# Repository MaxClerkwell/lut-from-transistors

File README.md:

# A look-up table built from transistors

A LUT with two inputs, the logic element of an FPGA, built from 20 MOS
transistors. The circuit is described in Python with
[SKiDL](https://devbisme.github.io/skidl/), drawn as a KiCad schematic,
simulated with ngspice, and the result is written as a VCD file that opens
in [GTKWave](https://gtkwave.sourceforge.net/).

```
SKiDL (lut.py)  ->  KiCad schematic  ->  ngspice  ->  VCD  ->  GTKWave
```

To run it yourself, see [Running the simulation](#running-the-simulation).

## What a LUT is

A LUT with k inputs does not compute anything. It stores the truth table of
a logic function in 2^k memory bits, and its inputs select which of these
bits appears at the output. With two inputs there are four bits and
therefore 16 possible functions, from AND to XOR, all realised by the same
hardware. Only the stored bits differ. That is what makes an FPGA
programmable.

```
T0 --[A=0]--+
            +-- N0 --[B=0]--+
T1 --[A=1]--+               +-- YI --|>o--|>o-- Y
T2 --[A=0]--+               |
            +-- N1 --[B=1]--+
T3 --[A=1]--+
```

The selection is a tree of 2:1 multiplexers, one level per input. The table
index is `2 B + A`. A buffer of two inverters restores the level and drives
the load.

## Configuration by voltage sources

The four table bits T0 to T3 are the configuration of the LUT. Here they
are voltage sources: 0 V for a 0, 5 V for a 1. In an FPGA they are memory
cells written by the bitstream. Replacing the cells by sources keeps the
circuit small and makes the configuration visible in the schematic: the
function of the LUT is the pattern of the four source values. The
simulation rewrites these sources every 800 ns and so steps through all 16
functions in one run.

## The switches

Each switch of the multiplexers is a transmission gate: an NMOS and a PMOS
in parallel, driven by complementary select signals. An NMOS alone passes
a 0 well but hands over a 1 only up to its gate voltage minus its
threshold; a PMOS alone has the opposite problem. Together they pass both
levels without loss, and the internal node YI reaches the full supply.
The price is one extra transistor per switch and the complements AN and BN
of the inputs, made by two inverters.

| Part | Transistors |
|---|---|
| 6 switches, 2 transistors each | 12 |
| 2 inverters for AN and BN | 4 |
| output buffer, 2 inverters | 4 |
| total | 20 |

## A hierarchical schematic

The schematic is hierarchical. Every building block is drawn once, on a
sheet of its own, and used as often as needed.

| Sheet | File | Content | Used |
|---|---|---|---|
| `lut2` | `lut2.kicad_sch` | sources, load, and the sheets below | 1 |
| `inverter` | `inverter.kicad_sch` | one PMOS, one NMOS | 4 |
| `mux2` | `mux2.kicad_sch` | two switches | 3 |
| `switch` | `switch.kicad_sch` | one transmission gate | 6 |
| `buffer` | `buffer.kicad_sch` | two inverters | 1 |

Five files describe 15 sheets. The hierarchy is three levels deep: the
transistors of a switch sit in `lut2 / mux_n0 / sw0`.

The root sheet shows the structure of the LUT: the supply, the inputs, the
four configuration sources, two inverters for the complements of the
inputs, two multiplexers selected by A, one selected by B, and the buffer.

In KiCad a sheet that is used several times stores the references of its
symbols once per use. The transistors of `switch.kicad_sch` are Q5 and Q6
in `mux_n0 / sw0` and Q15 and Q16 in `mux_y / sw1`. `hier.py` takes care
of this: it walks the hierarchy, creates the flat SKiDL circuit and writes
every sheet with the references of all its uses.

## Results

The LUT computes all 16 functions correctly: 64 of 64 table entries. All
numbers below are written by `simulate.py` to `results/summary.md`.

| Quantity | Value |
|---|---|
| Level of the internal node YI for a 1 | 5.00 V |
| Level of the output Y for a 1 | 5.00 V |
| Supply current at rest, largest | 0.015 µA |
| Delay A to Y, rising / falling | 12.2 ns / 9.1 ns |
| Delay B to Y, rising / falling | 10.8 ns / 7.8 ns |
| Delay table bit to Y, rising / falling | 11.1 ns / 8.2 ns |

What the numbers show:

- **The transmission gates pass the full level.** The internal node YI
  reaches 5 V for a 1 and 0 V for a 0, so the first inverter of the buffer
  is fully switched and the circuit draws almost no current at rest.
- **The input of the last level is the fastest.** A signal at B passes one
  multiplexer, a signal at A passes two. B is faster by about 1.4 ns.
  Synthesis tools use this and route timing-critical signals to the fast
  inputs of a LUT.
- **A change of configuration is as fast as a change of input.** A table
  bit passes two multiplexers, like A, and arrives at Y after a similar
  delay.

The plot shows one function window of 800 ns. During the first 100 ns the
table still holds the previous function; it is rewritten at 100 ns.

### Glitches

If both inputs change at the same instant, the multiplexer tree passes
through an intermediate state, even if the old and the new table entry are
the same. `simulate.py` tests this in a second run.

| Change | Lowest level of YI | Lowest level of Y |
|---|---|---|
| XOR, index 1 to 2 | 3.37 V | 5.00 V |
| XOR, index 2 to 1 | 3.58 V | 5.00 V |
| XNOR, index 0 to 3 | 3.14 V | 5.00 V |
| XNOR, index 3 to 0 | 3.74 V | 5.00 V |

The internal node dips, but the dip is too short for the buffer to follow.
With these transistors and this load no glitch reaches the output. That is
a property of this circuit, not of LUTs in general.

## Viewing the waveforms in GTKWave

```sh
gtkwave results/lut2.vcd results/lut2.gtkw
gtkwave results/lut2_glitch.vcd results/lut2_glitch.gtkw
```

The view shows the window from 4.8 µs to 5.6 µs: the table changes from
5 (NOT A) to 6 (XOR) at the marker, then the index steps through 0, 1, 3,
2, and `y` follows the table entry. The analog traces below show the
multiplexer nodes N0 and N1, the tree output YI, and the two stages of
the buffer.

The `.gtkw` file sets up the view: the table as a hexadecimal number, the
inputs, the selected index and the output as logic signals, and below them
the node voltages as analog traces.

| Signal | Kind | Content |
|---|---|---|
| `table[3:0]` | bit vector | the stored function, T3 T2 T1 T0 |
| `a`, `b`, `y` | bit | logic value, threshold at half the supply |
| `index[1:0]` | bit vector | `2 B + A`, the selected table entry |
| `v_a`, `v_b` | real | input voltages |
| `v_n0`, `v_n1` | real | outputs of the first multiplexer level |
| `v_yi` | real | output of the tree, before the buffer |
| `v_yb`, `v_y` | real | after the first and the second inverter |

VCD is a format for digital signals, but it also knows real numbers, and
GTKWave draws them as curves (Data Format, Analog). `vcd.py` is a writer of
about 100 lines without dependencies.

## The simulation

One transient run of 12.8 µs covers all 16 functions.

- The inputs step through the four combinations in Gray code, index
  0, 1, 3, 2, in steps of 200 ns. Only one input changes at a time, so
  every edge of the output can be attributed to one input.
- Every 800 ns the table bits are rewritten, 100 ns after the inputs have
  returned to 00. This is the simulation's version of loading a new
  bitstream.
- The output is sampled 5 ns before the end of every step and compared with
  the table.

The netlist that is simulated is exported from the KiCad schematic with
`kicad-cli`, which flattens the hierarchy, so the schematic is what gets
simulated.

## The paper

`paper/transistor_lut_en.tex` is a step-by-step introduction built on
this circuit: from Boolean functions and Shannon's expansion over the
transistor as a switch, the transmission gate and the CMOS inverter to
the complete LUT and its simulation, with every number in the text
computed from the model or taken from `results/summary.md`.

A GitHub Actions workflow runs on every push: it generates the schematic
in a KiCad container, checks it against the SKiDL netlist, simulates with
ngspice, checks that all 64 truth-table entries are correct, regenerates
the figures from the fresh results, builds the PDF and attaches it to
releases on version tags.

```sh
uv run scripts/make_figures.py       # figures from the model and results/
scripts/make_schematics.sh           # schematic sheets from docs/sheets/
cd paper && latexmk -pdf transistor_lut_en.tex
```

The figures are committed, so a LaTeX installation is enough to build
the PDF; the two scripts are needed only after a change of the circuit
or the simulation.

## Files

| File | Content |
|---|---|
| `lut.py` | the design: sheets `inverter`, `switch`, `mux2`, `buffer` and the root `lut2` |
| `hier.py` | hierarchy: elaborates the sheets into a flat SKiDL circuit and writes the KiCad sheets |
| `generate.py` | writes netlist and schematic, verifies the schematic against the SKiDL circuit |
| `simulate.py` | simulation, analysis, VCD and GTKWave files, plot |
| `vcd.py` | VCD writer |
| `kicad_sch.py`, `ngspice.py` | schematic writer and ngspice wrapper, from [naive-diff-amp-comperator](https://github.com/MaxClerkwell/naive-diff-amp-comperator) |
| `schematic/` | generated KiCad project: root sheet `lut2.kicad_sch`, four sub-sheets, netlist `lut2.net` |
| `docs/` | renderings: one SVG per sheet in `sheets/`, all sheets in `lut2.pdf` |
| `results/` | VCD and GTKWave files, plot, netlist, `summary.md` |
| `paper/` | the paper, `transistor_lut_en.tex`, and its figures |
| `scripts/` | `make_figures.py` and `make_schematics.sh`, the figure generators of the paper |

## Running the simulation

Requirements: [uv](https://docs.astral.sh/uv/), Python 3.10 or newer,
KiCad 9 or 10 with `kicad-cli` and the symbol libraries in
`/usr/share/kicad/symbols`, `libngspice.so.0`, and GTKWave for viewing.
`uv` installs the Python packages (SKiDL, NumPy, Matplotlib) on the first
run.

1. **Generate the schematic.** SKiDL builds the circuit from `lut.py`,
   `hier.py` writes the five KiCad sheets into `schematic/`, and
   `kicad-cli` renders them into `docs/`.

   ```sh
   uv run generate.py
   ```

   The last line must read `schematic <-> SKiDL netlist: IDENTICAL`. It
   means the schematic that KiCad reads describes the same circuit as the
   Python code. The step overwrites the schematic, including manual
   changes made in KiCad. KiCad's electrical rules check reports no
   violations.

2. **Simulate.** `kicad-cli` exports a flat SPICE netlist from the
   schematic, ngspice runs the transient analysis, and the script
   evaluates it.

   ```sh
   uv run simulate.py
   ```

   It takes a few seconds. The console ends with the truth table of all
   16 functions and the measured delays; the same text goes to
   `results/summary.md`. Along with it the script writes `results/lut2.vcd`
   and `results/lut2.gtkw`, the glitch run as `results/lut2_glitch.*`, the
   simulated netlist `results/lut2.cir` and the plot `results/lut2.png`.

3. **Open the result in GTKWave.** Give GTKWave the VCD file and the save
   file; the save file sets up the signal list and the analog traces.

   ```sh
   gtkwave results/lut2.vcd results/lut2.gtkw
   ```

   The view opens on the whole run of 12.8 µs. Zoom with `Ctrl` and the
   mouse wheel, or type a range into the `From` and `To` fields, for
   example `4800ns` and `5600ns` for the XOR window shown above. The
   signals are listed in [Viewing the waveforms in GTKWave](#viewing-the-waveforms-in-gtkwave).
   For the glitch experiment:

   ```sh
   gtkwave results/lut2_glitch.vcd results/lut2_glitch.gtkw
   ```

To look at the schematic, open the root sheet with
`eeschema schematic/lut2.kicad_sch`. A double click on a sheet symbol
enters the sheet.

## Limits

- **The transistor models are generic.** They are level-1 MOS models with
  plausible numbers: threshold 1 V, channel 10 µm by 10 µm, junction
  capacitance 0.5 pF. They describe neither a particular discrete part nor
  an FPGA process. The delays are properties of these models. A LUT in a
  modern FPGA switches in tens of picoseconds.
- **The configuration is ideal.** Voltage sources have no output
  resistance and are never disturbed by the circuit they drive. Memory
  cells in an FPGA are, and have to be dimensioned for it.
- **No layout.** Wiring capacitance and resistance are not part of the
  simulation. There is a single load of 10 pF at the output.
- **Four-terminal transistors.** The bulk of every NMOS is tied to ground
  and of every PMOS to the supply, as on a chip. Discrete MOSFETs with
  three terminals have bulk and source connected inside the package, and
  their body diode conducts in a transmission gate. For a build on a
  breadboard use an array with a separate bulk terminal, such as the
  CD4007.

## Acknowledgement

Parts of the documentation, the README and the paper, were revised with
Claude with the aim of better readability.

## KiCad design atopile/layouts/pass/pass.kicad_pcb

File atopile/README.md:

# The same LUT in atopile

The look-up table of this repository, described a second time in
[atopile](https://atopile.io) instead of Python and SKiDL.

| File | Content |
|---|---|
| `parts/MOS4/MOS4.ato` | the two transistors, NMOS4 and PMOS4, with four terminals |
| `blocks.ato` | `Inverter`, `SwitchTgate`, `SwitchPass`, `Mux2Tgate`, `Mux2Pass`, `Buffer`, `SramCell` |
| `lut2.ato` | the three variants `Lut2Tgate`, `Lut2Pass`, `Lut2Sram` |
| `ato.yaml` | one build per variant |
| `layouts/<variant>/<variant>.kicad_pcb` | result of the build: footprints and nets |

Modules, instances and ports have the same names as the sheets generated
from `lut.py`. An inverter in atopile:

```
module Inverter:
    power = new ElectricPower
    signal IN
    signal OUT

    qp = new PMOS4
    qn = new NMOS4

    qp.G ~ IN
    qn.G ~ IN
    qp.D ~ OUT
    qn.D ~ OUT
    qp.S ~ power.hv
    qp.B ~ power.hv
    qn.S ~ power.lv
    qn.B ~ power.lv
```

`Lut2Sram` is derived from `Lut2Tgate` and adds the four memory cells.

## What atopile produces, and what it does not

atopile is a tool for designing boards. It compiles the description into a
KiCad board file with one footprint per component and the net of every pad.

| Output | atopile | This repository |
|---|---|---|
| netlist | yes, inside the board file | read back by `ato_netlist.py` |
| board with footprints | yes | not used; the transistors are generic |
| schematic | no | drawn by `hier.py` from `lut.py` |
| SPICE netlist | no | written by `simulate.py --source atopile` |
| sources, test bench | not part of a board | added by `simulate.py` |

So atopile replaces SKiDL as the description of the circuit, but not the
rest of the chain. The schematics still come from `lut.py`, because only
that description contains the placement of the symbols.

## Verification

```sh
uv run verify_atopile.py                 # from the repository root
uv run simulate.py --source atopile
```

`verify_atopile.py` compares the atopile build with the design in `lut.py`:
the same transistors, of the same type, at the same place in the hierarchy,
and every net connecting the same pins. References differ between the two,
so parts are identified by their address, such as `mux_n0.sw0.qn`.

| Variant | Transistors | Nets | Parts | Connectivity |
|---|---|---|---|---|
| `tgate` | 20 | 15 | identical | identical |
| `pass` | 14 | 11 | identical | identical |
| `sram` | 44 | 25 | identical | identical |

The simulation from the atopile netlist gives the same numbers as the
simulation from the KiCad schematic, digit by digit
(`results/atopile/summary.md` and `results/summary.md`).

## Building

The board files are committed, so verification and simulation work without
atopile. To rebuild:

```sh
ATO=/path/to/ato ./build.sh
```

Built with atopile 0.15.8 on Python 3.14.

## Things to know about atopile

- **The command line is at the end of its life.** Version 0.15.8 is the
  last release of the classic command line and in maintenance mode. From
  0.16 on atopile is an application at app.atopile.io. This project uses
  the command line only, locally.
- **atopile changes the KiCad configuration.** On every start it writes a
  plugin loader into KiCad's scripting directory and enables the KiCad API
  server in `kicad_common.json`. `build.sh` prevents this by giving atopile
  a home directory of its own.
- **Every component has to be a purchasable part.** A component needs a
  footprint and a supplier part number, and LCSC is the only supplier
  atopile accepts. The generic transistors of this design therefore carry
  a SOT-143 footprint and the placeholder `PLACEHOLDER-NMOS4` as part
  number. This is not a real LCSC number and nothing can be ordered with
  it. `build.sh` runs without network access, so nothing is looked up.
- **Net names** are chosen by atopile unless they are set. `lut2.ato` sets
  them for the signals of the top level with `override_net_name`. For the
  supply this had no effect; the nets are called `hv` and `lv`.
- **The footprint** `SOT-143.kicad_mod` is a copy from the KiCad footprint
  library, which is licensed CC BY-SA 4.0 with an exception for use in
  designs.

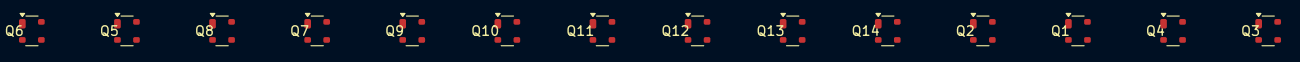
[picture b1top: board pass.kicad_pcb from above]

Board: 2 copper layers, 14 parts (0 on the bottom side), 11 nets, no tracks yet.

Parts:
Q1, Q2, Q3, Q4, Q5, Q6, Q7, Q8, Q9, Q10, Q11, Q12, Q13, Q14: SOT-143

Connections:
A: Q5.2, Q6.2, Q10.2, Q12.2
AN: Q5.1, Q6.1, Q9.2, Q11.2
B: Q7.2, Q8.2, Q14.2
BN: Q7.1, Q8.1, Q13.2
BUFFER_MID: Q1.1, Q2.1, Q3.2, Q4.2
N0: Q9.3, Q10.3, Q13.1
N1: Q11.3, Q12.3, Q14.1
Y: Q3.1, Q4.1
YI: Q1.2, Q2.2, Q13.3, Q14.3
hv: Q2.3, Q2.4, Q4.3, Q4.4, Q6.3, Q6.4, Q8.3, Q8.4
lv: Q1.3, Q1.4, Q3.3, Q3.4, Q5.3, Q5.4, Q7.3, Q7.4, Q9.4, Q10.4, Q11.4, Q12.4, Q13.4, Q14.4

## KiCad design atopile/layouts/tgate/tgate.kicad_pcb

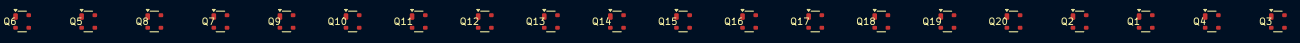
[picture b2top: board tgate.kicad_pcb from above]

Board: 2 copper layers, 20 parts (0 on the bottom side), 15 nets, no tracks yet.

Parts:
Q1, Q2, Q3, Q4, Q5, Q6, Q7, Q8, Q9, Q10, Q11, Q12, Q13, Q14, Q15, Q16, Q17, Q18, Q19, Q20: SOT-143

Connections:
A: Q5.2, Q6.2, Q10.2, Q11.2, Q14.2, Q15.2
AN: Q5.1, Q6.1, Q9.2, Q12.2, Q13.2, Q16.2
B: Q7.2, Q8.2, Q18.2, Q19.2
BN: Q7.1, Q8.1, Q17.2, Q20.2
BUFFER_MID: Q1.1, Q2.1, Q3.2, Q4.2
N0: Q9.3, Q10.1, Q11.3, Q12.1, Q17.1, Q18.3
N1: Q13.3, Q14.1, Q15.3, Q16.1, Q19.1, Q20.3
T0: Q9.1, Q10.3
T1: Q11.1, Q12.3
T2: Q13.1, Q14.3
T3: Q15.1, Q16.3
Y: Q3.1, Q4.1
YI: Q1.2, Q2.2, Q17.3, Q18.1, Q19.3, Q20.1
hv: Q2.3, Q2.4, Q4.3, Q4.4, Q6.3, Q6.4, Q8.3, Q8.4, Q10.4, Q12.4, Q14.4, Q16.4, Q18.4, Q20.4
lv: Q1.3, Q1.4, Q3.3, Q3.4, Q5.3, Q5.4, Q7.3, Q7.4, Q9.4, Q11.4, Q13.4, Q15.4, Q17.4, Q19.4

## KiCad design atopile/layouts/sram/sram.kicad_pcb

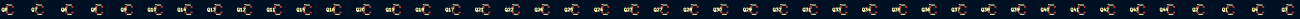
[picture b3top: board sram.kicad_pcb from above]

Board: 2 copper layers, 44 parts (0 on the bottom side), 25 nets, no tracks yet.

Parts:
Q1, Q2, Q3, Q4, Q5, Q6, Q7, Q8, Q9, Q10, Q11, Q12, Q13, Q14, Q15, Q16, Q17, Q18, Q19, Q20, Q21, Q22, Q23, Q24, Q25, Q26, Q27, Q28, Q29, Q30, Q31, Q32, Q33, Q34, Q35, Q36, Q37, Q38, Q39, Q40, Q41, Q42, Q43, Q44: SOT-143

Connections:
A: Q29.2, Q30.2, Q34.2, Q35.2, Q38.2, Q39.2
AN: Q29.1, Q30.1, Q33.2, Q36.2, Q37.2, Q40.2
B: Q31.2, Q32.2, Q42.2, Q43.2
BL: Q9.1, Q15.1, Q21.1, Q27.1
BLN: Q10.3, Q16.3, Q22.3, Q28.3
BN: Q31.1, Q32.1, Q41.2, Q44.2
BUFFER_MID: Q1.1, Q2.1, Q3.2, Q4.2
D: Q5.1, Q6.1, Q7.2, Q8.2, Q10.1
N0: Q33.3, Q34.1, Q35.3, Q36.1, Q41.1, Q42.3
N1: Q37.3, Q38.1, Q39.3, Q40.1, Q43.1, Q44.3
T0: Q5.2, Q6.2, Q7.1, Q8.1, Q9.3, Q33.1, Q34.3
T1: Q11.2, Q12.2, Q13.1, Q14.1, Q15.3, Q35.1, Q36.3
T2: Q17.2, Q18.2, Q19.1, Q20.1, Q21.3, Q37.1, Q38.3
T3: Q23.2, Q24.2, Q25.1, Q26.1, Q27.3, Q39.1, Q40.3
WL0: Q9.2, Q10.2
WL1: Q15.2, Q16.2
WL2: Q21.2, Q22.2
WL3: Q27.2, Q28.2
Y: Q3.1, Q4.1
YI: Q1.2, Q2.2, Q41.3, Q42.1, Q43.3, Q44.1
cell1-D: Q11.1, Q12.1, Q13.2, Q14.2, Q16.1
cell2-D: Q17.1, Q18.1, Q19.2, Q20.2, Q22.1
cell3-D: Q23.1, Q24.1, Q25.2, Q26.2, Q28.1
hv: Q2.3, Q2.4, Q4.3, Q4.4, Q6.3, Q6.4, Q8.3, Q8.4, Q12.3, Q12.4, Q14.3, Q14.4, Q18.3, Q18.4, Q20.3, Q20.4, Q24.3, Q24.4, Q26.3, Q26.4, Q30.3, Q30.4, Q32.3, Q32.4, Q34.4, Q36.4, Q38.4, Q40.4, Q42.4, Q44.4
lv: Q1.3, Q1.4, Q3.3, Q3.4, Q5.3, Q5.4, Q7.3, Q7.4, Q9.4, Q10.4, Q11.3, Q11.4, Q13.3, Q13.4, Q15.4, Q16.4, Q17.3, Q17.4, Q19.3, Q19.4, Q21.4, Q22.4, Q23.3, Q23.4, Q25.3, Q25.4, Q27.4, Q28.4, Q29.3, Q29.4, Q31.3, Q31.4, Q33.4, Q35.4, Q37.4, Q39.4, Q41.4, Q43.4
